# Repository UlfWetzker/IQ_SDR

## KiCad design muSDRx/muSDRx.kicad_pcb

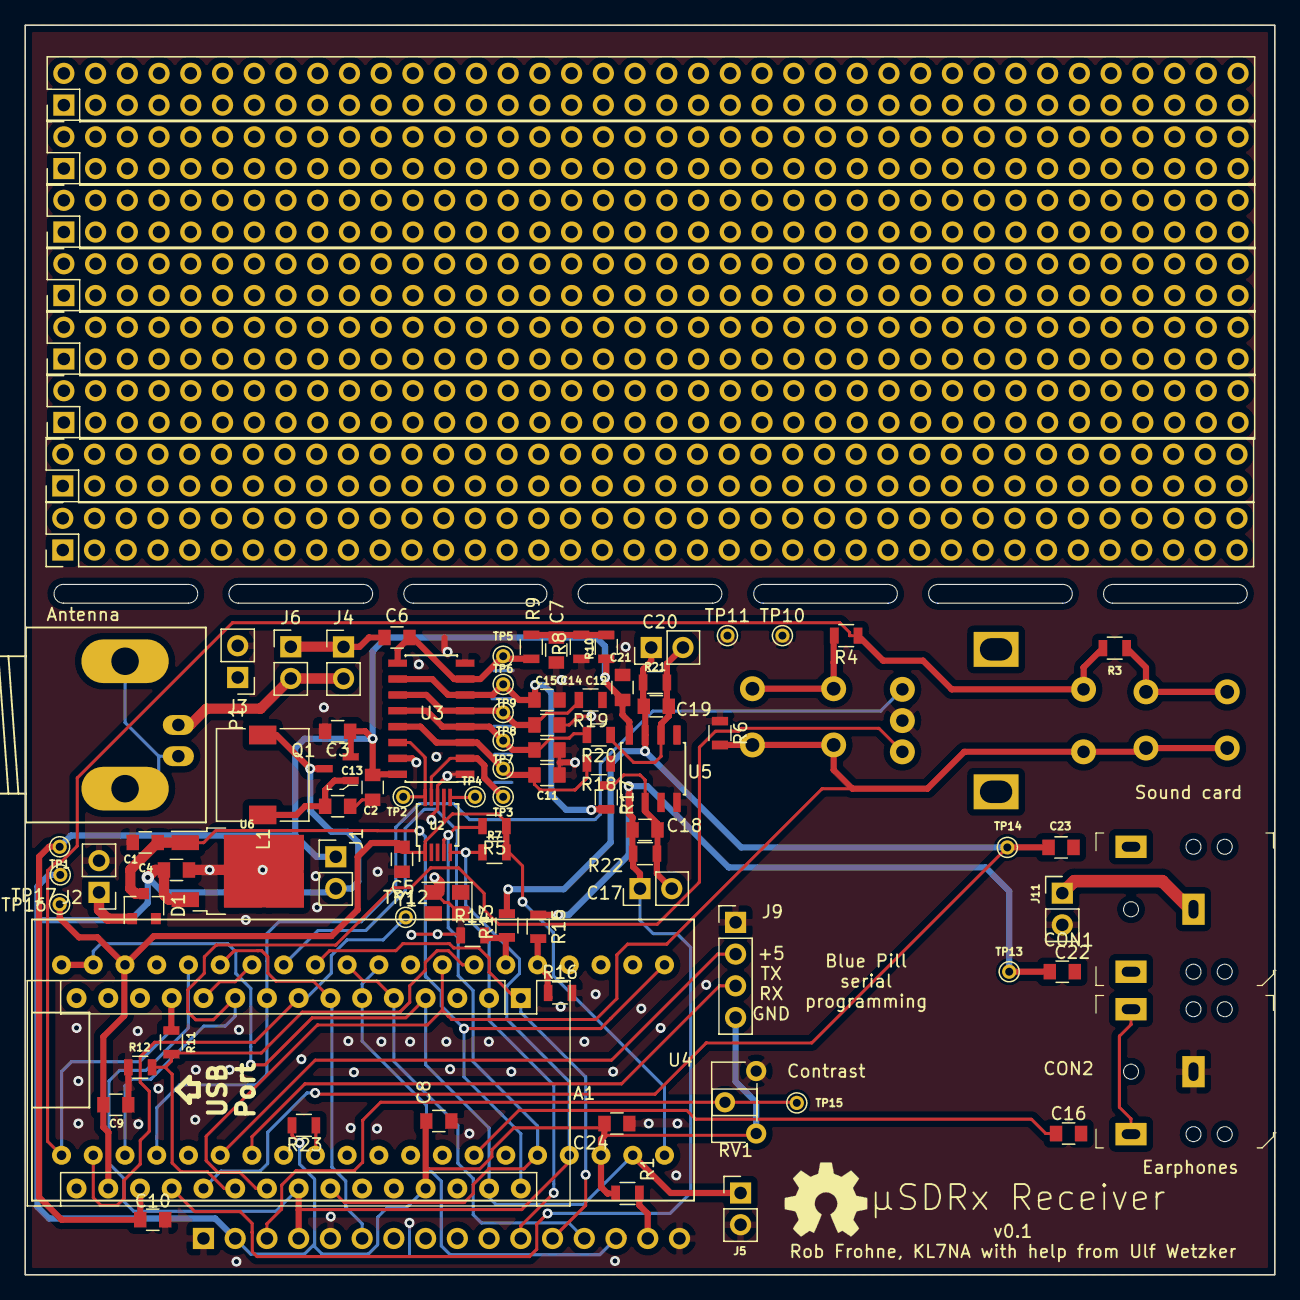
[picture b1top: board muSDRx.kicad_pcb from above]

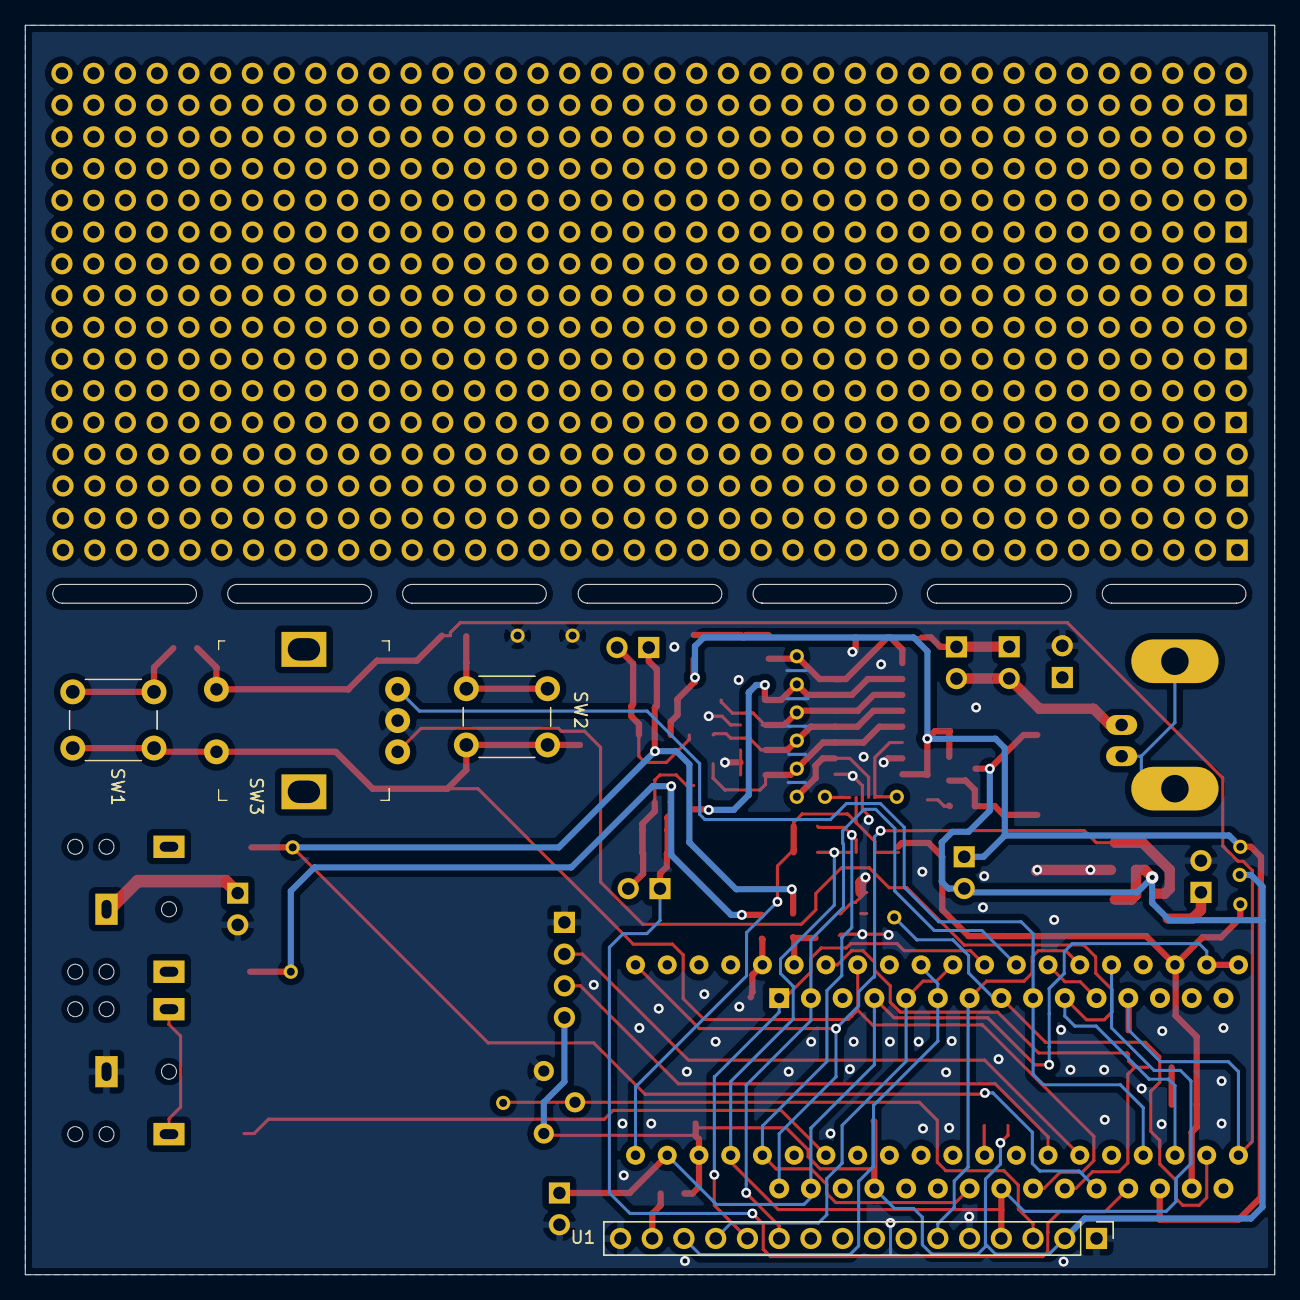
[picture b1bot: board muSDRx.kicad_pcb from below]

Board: 2 copper layers, 100.0 x 100.0 mm, 97 parts (4 on the bottom side), 49 nets.

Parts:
A1: Arduino_Nano_v3.x; Arduino_Nano
C1, C3: 1uF; C_0805
C2, C4, C16, C22, C23: 10uF; C_0805
C5, C6, C7, C8, C9, C10, C13, C21, C24: 0.1uF; C_0805
C11, C12, C14, C15: 0.47uF; C_0805
C17, C20: 1nF; Pin_Header_Straight_1x02_Pitch2.54mm
C18, C19: 20pF; C_0805
CON1, CON2: SJ1-3523N; Headphone_Jack_2.5mm_SJ1-3523N
D1: MMBD4148; D_SOT-23_ANK
J1, J2, J3, J4, J5, J6, J11: Conn_01x02_Male; Pin_Header_Straight_1x02_Pitch2.54mm
J9: Conn_01x04_Male; Pin_Header_Straight_1x04_Pitch2.54mm
L1: 300uH; L_7.3x7.3_H4.5
P1: BNC; BNC_Socket_TYCO-AMP_LargePads
Q1: MMBT2222A-TP; SOT-23-3
R1, R3, R5, R7, R9, R13, R15, R23: 1k; R_0805
R4: 3.3k; R_0805
R6, R8, R10, R11, R12: 10k; R_0805
R14, R16: 11k; R_0805
R17, R18, R19, R20: 100; R_0805
R21, R22: 82k; R_0805
REF1, REF2, REF3, REF4, REF5, REF6, REF7, REF8: Pin_Header_Straight_2x38_Pitch2.54mm
RV1: 10k; Potentiometer_Trimmer_ACP_CA6h_Vertical
SW1, SW2: SW_Push; SW_PUSH_6mm_h4.3mm
SW3: Rotary_Encoder_Switch; Rotary_Encoder_Switched_PEC11R
TP1, TP2, TP3, TP4, TP5, TP6, TP7, TP8, TP9, TP10, TP11, TP12, TP13, TP14, TP15, TP16, TP17: TestPoint; PINTST
U1: LCD1602; Pin_Header_Straight_1x16_Pitch2.54mm
U2: Si5351A-B-GT; MSOP-10_3x3mm_Pitch0.5mm
U3: SN74CBT3253; SOIC-16_3.9x9.9mm_Pitch1.27mm
U4: BluePill; BLUEPILL
U5: LT6231 (or LM4562); SOIC-8_3.9x4.9mm_Pitch1.27mm
U6: MC78M05_TO252; TO-252-2
Y1: CX3225; Crystal_SMD_Abracon_ABM8G-4pin_3.2x2.5mm

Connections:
+3V3: A1.17, C5.1, C9.1, R5.2, R7.2, TP16.1, U2.1, U2.7, U4.3V3
+4.3V: A1.18, C3.1, C10.1, C13.1, C21.1, J1.1, Q1.2, R10.1, TP1.1, U3.16, U5.8
+5V: A1.27, C4.1, C8.1, C24.1, J1.2, J9.4, L1.1, Q1.3, R1.1, R23.1, RV1.1, TP17.1, U1.2, U4.5V, U6.3
/2F: TP3.1, U2.9, U3.2
/4F: TP2.1, U2.10, U3.14
/AUD_0: A1.19, C17.1, C18.1, C22.2, R15.1, R22.1, TP13.1, U5.1
/AUD_1: A1.20, C19.1, C20.1, C23.2, R13.1, R21.1, TP14.1, U5.7
/BUTTON: A1.22, R6.2, SW1.2, SW2.2, SW3.S1, U4.PA3
/D4: A1.2, U1.11, U4.PB0
/D5: A1.1, U1.12, U4.PA7
/D6: A1.5, U1.13, U4.PA6
/D7: A1.6, U1.14, U4.PA5
/DVM: A1.21, R11.2, R12.1, U4.PA2
/EN: A1.7, U1.6, U4.PB10
/FREQ_COUNT: A1.8, TP12.1, U4.PB13
/ROT_A: A1.10, SW3.A, U4.PB14
/ROT_B: A1.9, SW3.B, U4.PB15
/RS: A1.23, R7.1, U1.4, U2.5, U4.PB9, U4.PB11
/RX: A1.11, U4.PB1
/SCL: A1.24, R5.1, U2.4, U4.PB8
/SIG_OUT: J9.2, U4.PA9
/VHI: A1.12, R3.2, R4.2, R11.1, SW3.S2, U4.PB12
/V_IN: A1.30, C1.1, D1.3, U4.VBAT, U6.1
GND: C1.2, C2.2, C3.2, C4.2, C5.2, C7.2, C8.2, C9.2, C10.2, C11.2, C12.2, C13.2, C14.2, C15.2, C21.2, C24.2, CON2.1, J2.2, J3.2, J5.2, J9.1, J11.2, R6.1, R8.2, R12.2, R14.2, R16.2, RV1.3, SW3.C, TP10.1, TP11.1, U1.1, U1.5, U1.16, U2.8, U3.1, U3.8, U3.15, U5.4, U6.2, Y1.2, Y1.4
unnamed: A1.4, A1.29, J5.1, U4.G
unnamed: C2.1, L1.2, Q1.1
unnamed: C6.1, R9.2, TP5.1, U3.7, U3.9
unnamed: C6.2, J4.1, J6.1
unnamed: C7.1, R8.1, R9.1, R10.2
unnamed: C11.1, R18.2, TP7.1, U3.3, U3.13
unnamed: C12.1, R20.2, TP8.1, U3.4, U3.12
unnamed: C14.1, R19.2, TP9.1, U3.5, U3.11
unnamed: C15.1, R17.2, TP6.1, U3.6, U3.10
unnamed: CON2.2, CON2.3
unnamed: C16.2, U4.PB6
unnamed: C17.2, C18.2, R17.1, R22.2, U5.2
unnamed: C19.2, C20.2, R20.1, R21.2, U5.6
unnamed: CON1.1, J11.1
unnamed: D1.1, J2.1
unnamed: J4.2, J6.2, P1.1
unnamed: J9.3, U4.PA10
unnamed: R1.2, U1.15
unnamed: R3.1, SW1.1
unnamed: R4.1, SW2.1
unnamed: R13.2, R14.1, U4.PA1
unnamed: R15.2, R16.1, U4.PA0
unnamed: R23.2, U4.PA12
unnamed: RV1.2, TP15.1, U1.3
unnamed: TP4.1, U2.6

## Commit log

2020-07-08 Added MCP1802 to symtable
2020-07-09 Fixed library references
2020-07-09 Rerouted analog section
2020-07-12 Rerouted digital section
2020-07-12 Fix libriary references
